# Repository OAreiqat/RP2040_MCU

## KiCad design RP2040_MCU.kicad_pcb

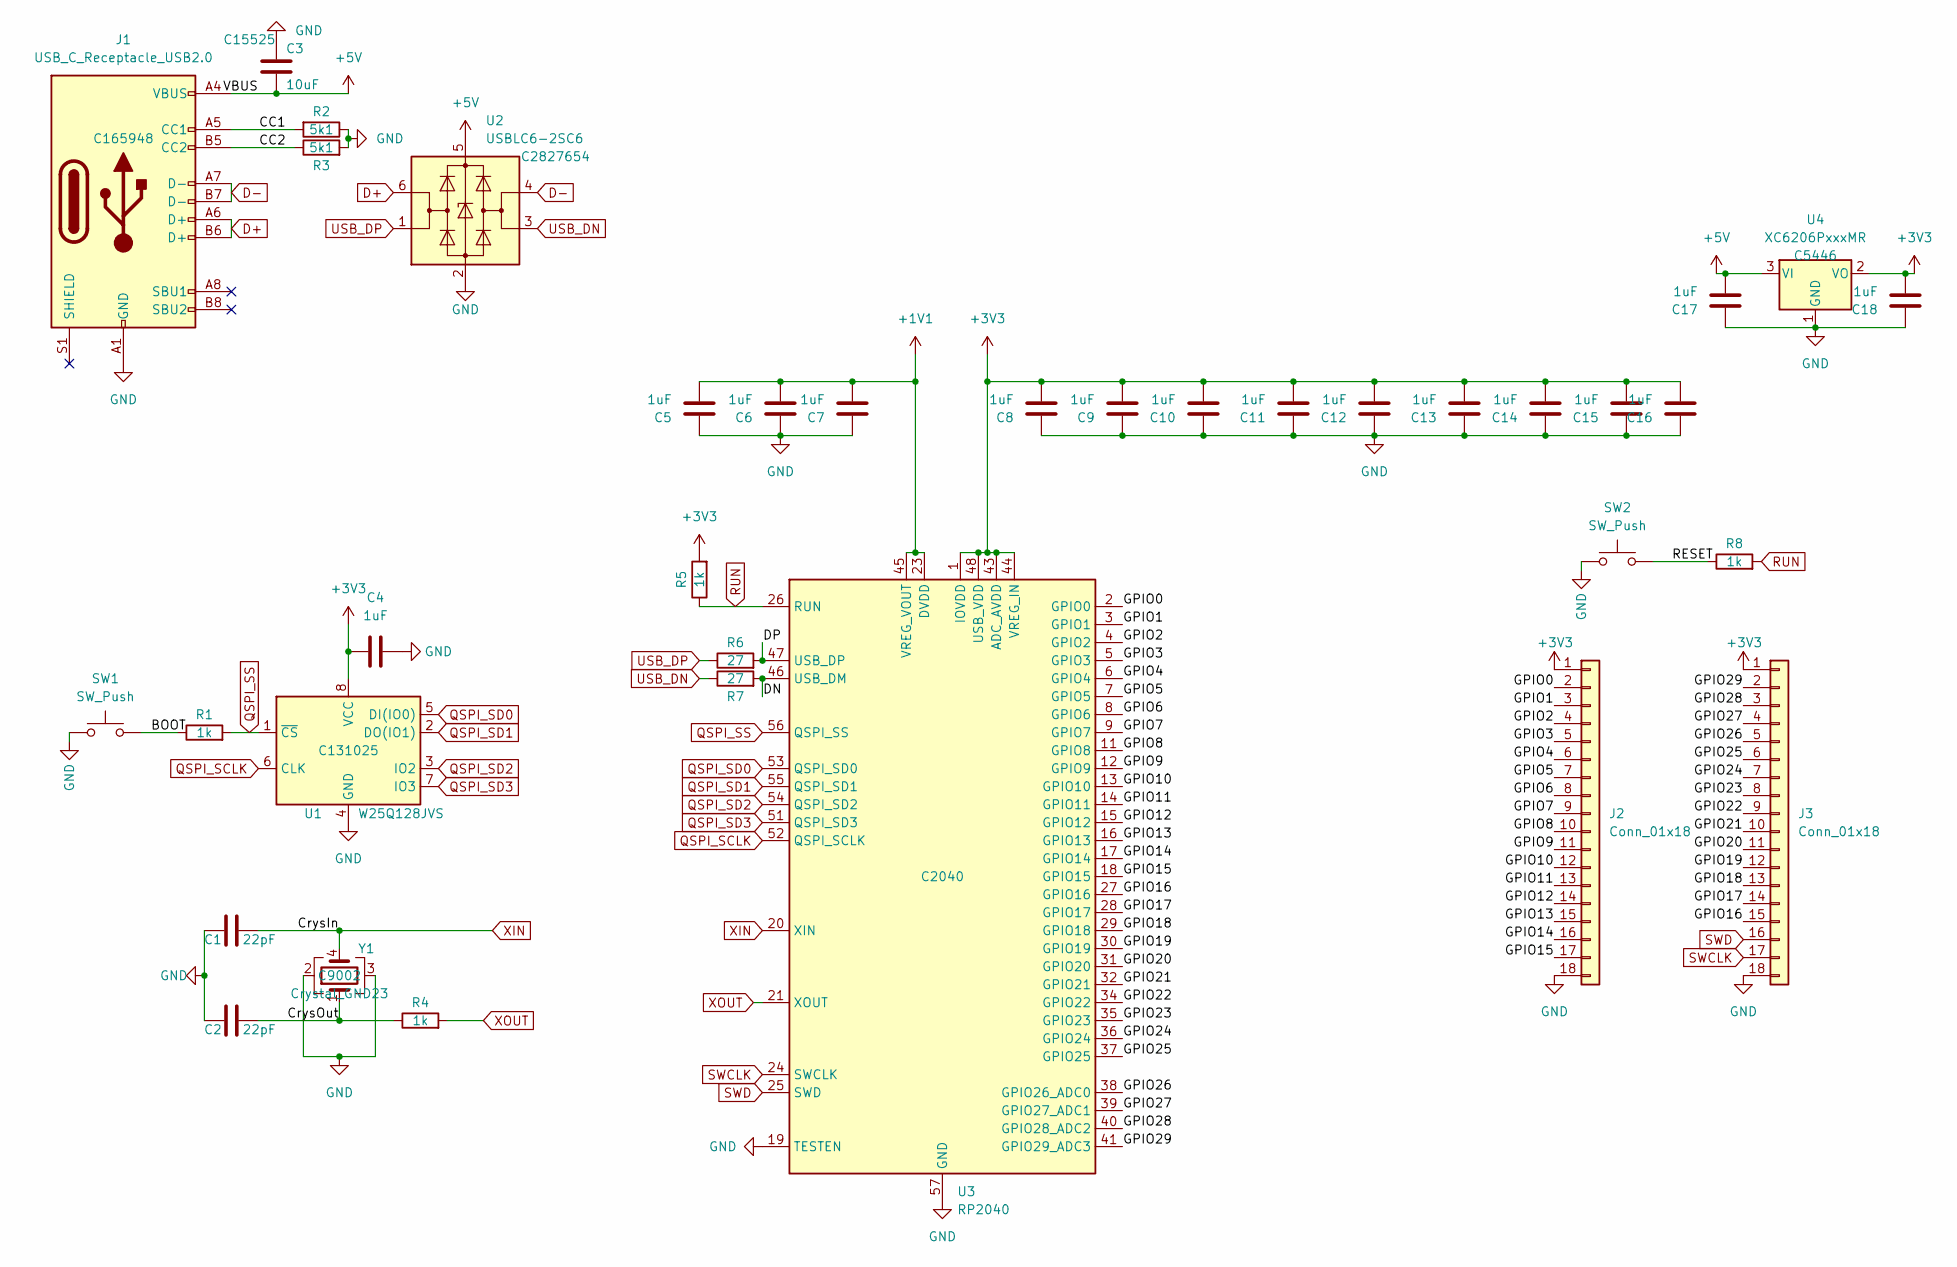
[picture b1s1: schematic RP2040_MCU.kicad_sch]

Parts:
C1, C2: 22pF; C_0603_1608Metric; LCSC C1555
C3: 10uF; C_0603_1608Metric; LCSC C15525
C4, C5, C6, C7, C8, C9, C10, C11, C12, C13, C14, C15, C16, C17, C18: 1uF; C_0603_1608Metric; LCSC C52923
J1: USB_C_Receptacle_USB2.0; USB_C_Receptacle_HRO_TYPE-C-31-M-12; LCSC C165948
J2, J3: Conn_01x18; PinSocket_1x18_P2.54mm_Vertical
R1, R4, R5, R8: 1k; R_0603_1608Metric
R2, R3: 5k1; R_0603_1608Metric; LCSC C25905
R6, R7: 27; R_0603_1608Metric; LCSC C25190
SW1: SW_Push; SW_Push_SPST_NO_Alps_SKRK
SW2: SW_Push; SW_Push_SPST_NO_Alps_SKRK; LCSC C720477
U1: W25Q128JVS; SOIC-8_5.23x5.23mm_P1.27mm; LCSC C131025
U2: USBLC6-2SC6; SOT-23-6; LCSC C2827654
U3: RP2040; QFN-56-1EP_7x7mm_P0.4mm_EP3.2x3.2mm; LCSC C2040
U4: XC6206PxxxMR; SOT-23; LCSC C5446
Y1: Crystal_GND23; Crystal_SMD_3225-4Pin_3.2x2.5mm; LCSC C9002

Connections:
+1V1: C5.2, C6.2, C7.2, U3.23 (DVDD), U3.45 (VREG_VOUT), U3.50 (DVDD)
+3V3: C4.2, C8.2, C9.2, C10.2, C11.2, C12.2, C13.2, C14.2, C15.2, C16.2, C18.2, J2.1, J3.1, R5.2, U1.8 (VCC), U3.1 (IOVDD), U3.10 (IOVDD), U3.22 (IOVDD), U3.33 (IOVDD), U3.42 (IOVDD), U3.43 (ADC_AVDD), U3.44 (VREG_IN), U3.48 (USB_VDD), U3.49 (IOVDD), U4.2 (VO)
+5V: C3.2, C17.2, J1.A4 (VBUS), J1.A9 (VBUS), J1.B4 (VBUS), J1.B9 (VBUS), U2.5 (VBUS), U4.3 (VI)
/BOOT: R1.1, SW1.2
/CC1: J1.A5 (CC1), R2.2
/CC2: J1.B5 (CC2), R3.1
/CrysOut: C2.1, R4.1, Y1.1
/DN: R7.2, U3.46 (USB_DM)
/DP: R6.2, U3.47 (USB_DP)
/GPIO0: J2.2, U3.2 (GPIO0)
/GPIO1: J2.3, U3.3 (GPIO1)
/GPIO2: J2.4, U3.4 (GPIO2)
/GPIO3: J2.5, U3.5 (GPIO3)
/GPIO4: J2.6, U3.6 (GPIO4)
/GPIO5: J2.7, U3.7 (GPIO5)
/GPIO6: J2.8, U3.8 (GPIO6)
/GPIO7: J2.9, U3.9 (GPIO7)
/GPIO8: J2.10, U3.11 (GPIO8)
/GPIO9: J2.11, U3.12 (GPIO9)
/GPIO10: J2.12, U3.13 (GPIO10)
/GPIO11: J2.13, U3.14 (GPIO11)
/GPIO12: J2.14, U3.15 (GPIO12)
/GPIO13: J2.15, U3.16 (GPIO13)
/GPIO14: J2.16, U3.17 (GPIO14)
/GPIO15: J2.17, U3.18 (GPIO15)
/GPIO16: J3.15, U3.27 (GPIO16)
/GPIO17: J3.14, U3.28 (GPIO17)
/GPIO18: J3.13, U3.29 (GPIO18)
/GPIO19: J3.12, U3.30 (GPIO19)
/GPIO20: J3.11, U3.31 (GPIO20)
/GPIO21: J3.10, U3.32 (GPIO21)
/GPIO22: J3.9, U3.34 (GPIO22)
/GPIO23: J3.8, U3.35 (GPIO23)
/GPIO24: J3.7, U3.36 (GPIO24)
/GPIO25: J3.6, U3.37 (GPIO25)
/GPIO26: J3.5, U3.38 (GPIO26_ADC0)
/GPIO27: J3.4, U3.39 (GPIO27_ADC1)
/GPIO28: J3.3, U3.40 (GPIO28_ADC2)
/GPIO29: J3.2, U3.41 (GPIO29_ADC3)
/RESET: R8.1, SW2.2
D+: J1.A6 (D+), J1.B6 (D+), U2.6 (I/O1)
D-: J1.A7 (D-), J1.B7 (D-), U2.4 (I/O2)
GND: C1.2, C2.2, C3.1, C4.1, C5.1, C6.1, C7.1, C8.1, C9.1, C10.1, C11.1, C12.1, C13.1, C14.1, C15.1, C16.1, C17.1, C18.1, J1.A1 (GND), J1.A12 (GND), J1.B1 (GND), J1.B12 (GND), J2.18, J3.18, R2.1, R3.2, SW1.1, SW2.1, U1.4 (GND), U2.2 (GND), U3.19 (TESTEN), U3.57 (GND), U4.1 (GND), Y1.2, Y1.3
QSPI_SCLK: U1.6 (CLK), U3.52 (QSPI_SCLK)
QSPI_SD0: U1.5 (DI(IO0)), U3.53 (QSPI_SD0)
QSPI_SD1: U1.2 (DO(IO1)), U3.55 (QSPI_SD1)
QSPI_SD2: U1.3 (IO2), U3.54 (QSPI_SD2)
QSPI_SD3: U1.7 (IO3), U3.51 (QSPI_SD3)
QSPI_SS: R1.2, U1.1 (~CS), U3.56 (QSPI_SS)
RUN: R5.1, R8.2, U3.26 (RUN)
SWCLK: J3.17, U3.24 (SWCLK)
SWD: J3.16, U3.25 (SWD)
USB_DN: R7.1, U2.3 (I/O2)
USB_DP: R6.1, U2.1 (I/O1)
XIN: C1.1, U3.20 (XIN), Y1.4
XOUT: R4.2, U3.21 (XOUT)

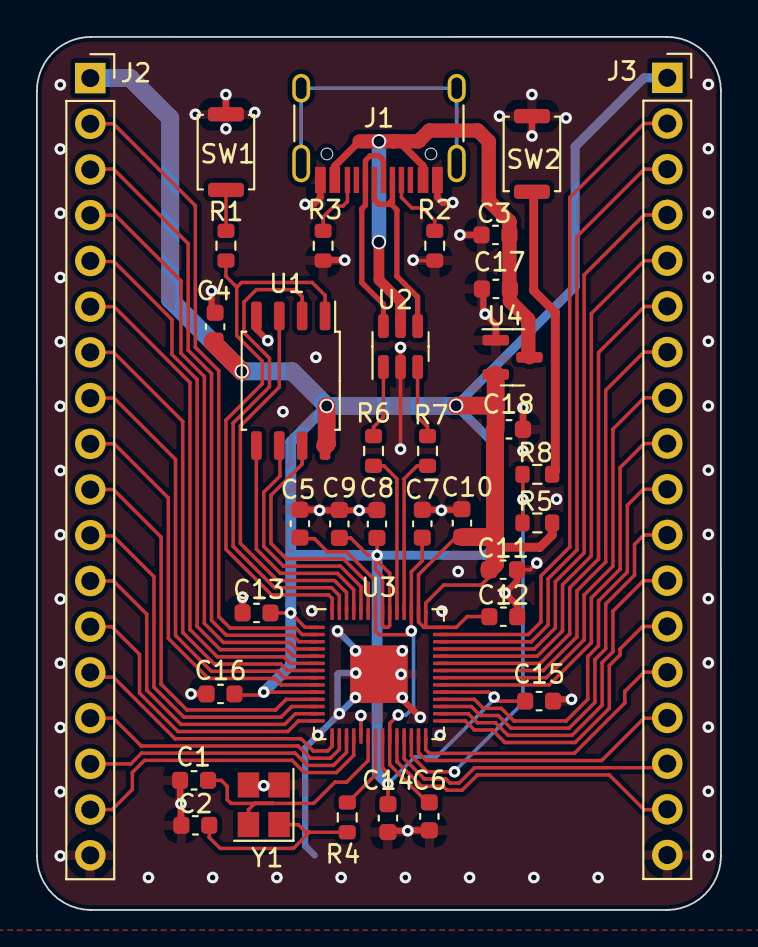
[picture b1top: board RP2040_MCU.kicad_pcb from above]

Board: 2 copper layers, 38.0 x 48.5 mm, 36 parts (0 on the bottom side), 56 nets.

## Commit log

2022-12-30 Added Design rules and placed rp2040
2022-12-31 Finished Schematic of RP2040 MCU
2022-12-31 Routing in Progress
2023-01-01 finished routing
2023-01-01 Finished Board. Need to double check and review
2023-01-01 fixed gpio traces
